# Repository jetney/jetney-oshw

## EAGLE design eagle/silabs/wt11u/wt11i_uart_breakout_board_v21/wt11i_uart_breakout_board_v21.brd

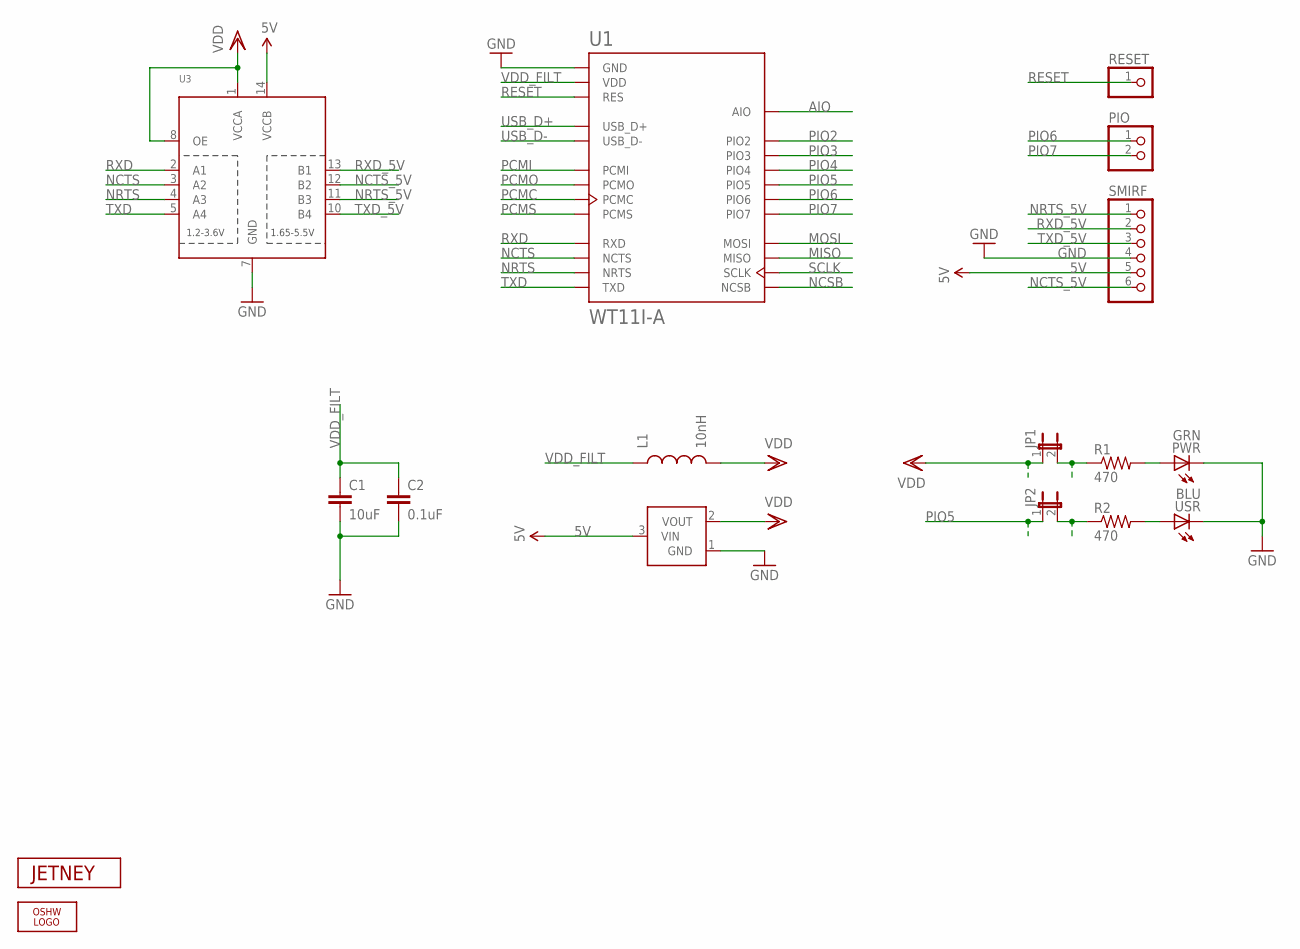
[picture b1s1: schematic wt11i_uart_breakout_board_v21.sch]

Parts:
C1: 10uF; 0603-CAP
C2: 0.1uF; 0603-CAP
JP1, JP2: JUMPER-2SMD-NC; SJ_2S
L1: 10nH; 0603
LOGO1: OSHW_LOGO_FILLX0070-NT; OSHW_FILLX70_NOTEXT
PIO: PINHD-1X2; 1X02
PWR: GRN; CHIPLED_0805
R1, R2: 470; 0603-RES
RESET: PINHD-1X1; 1X01
SMIRF: PINHD-1X6; 1X06
U1: WT11I-A
U2: MCP1700; SOT23-3
U3: TXB0104PWR; TSSOP14
U$4: JETNEY-LOGO-12
USR: BLU; CHIPLED_0805

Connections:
5V: SMIRF.5, U2.3 (VIN), U3.14 (VCCB)
AIO: U1.AIO
GND: C1.2, C2.2, PWR.C, SMIRF.4, U1.GND, U1.GND@2 (GND), U1.GND@3 (GND), U1.GND@4 (GND), U2.1 (GND), U3.7 (GND), USR.C
MISO: U1.MISO
MOSI: U1.MOSI
unnamed: PWR.A, R1.2
unnamed: R2.2, USR.A
unnamed: JP2.2, R2.1
NCSB: U1.NCSB
NCTS: U1.NCTS, U3.3 (A2)
NCTS_5V: SMIRF.6, U3.12 (B2)
NRTS: U1.NRTS, U3.4 (A3)
NRTS_5V: SMIRF.1, U3.11 (B3)
PCMC: U1.PCMC
PCMI: U1.PCMI
PCMO: U1.PCMO
PCMS: U1.PCMS
PIO2: U1.PIO2
PIO3: U1.PIO3
PIO4: U1.PIO4
PIO5: JP2.1, U1.PIO5
PIO6: PIO.1, U1.PIO6
PIO7: PIO.2, U1.PIO7
RESET: RESET.1, U1.RES
RXD: U1.RXD, U3.2 (A1)
RXD_5V: SMIRF.2, U3.13 (B1)
SCLK: U1.SCLK
TXD: U1.TXD, U3.5 (A4)
TXD_5V: SMIRF.3, U3.10 (B4)
USB_D+: U1.USB_D+
USB_D-: U1.USB_D-
VDD: JP1.1, L1.2, U2.2 (VOUT), U3.1 (VCCA), U3.8 (OE)
VDDJP1: JP1.2, R1.1
VDD_FILT: C1.1, C2.1, L1.1, U1.VDD, U1.VDD@2 (VDD)

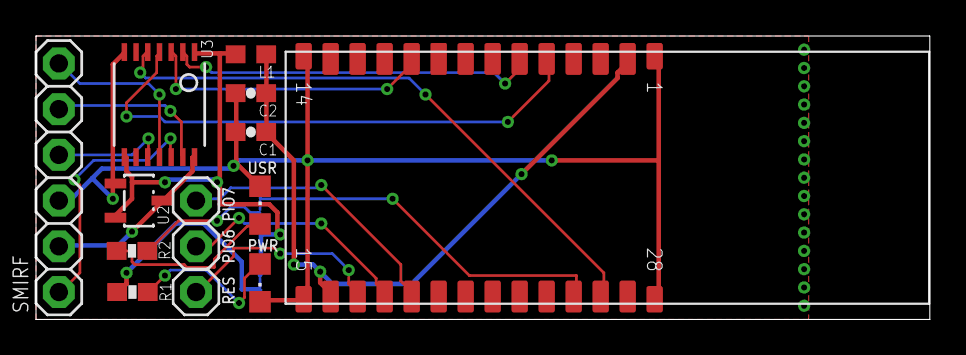
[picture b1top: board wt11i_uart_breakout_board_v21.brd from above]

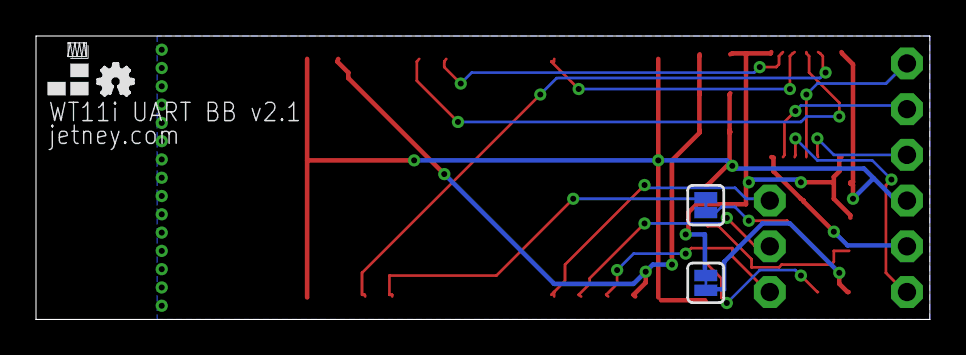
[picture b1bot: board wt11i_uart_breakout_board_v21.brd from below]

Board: 2 copper layers, 49.7 x 15.7 mm, 17 parts (4 on the bottom side), 20 nets.

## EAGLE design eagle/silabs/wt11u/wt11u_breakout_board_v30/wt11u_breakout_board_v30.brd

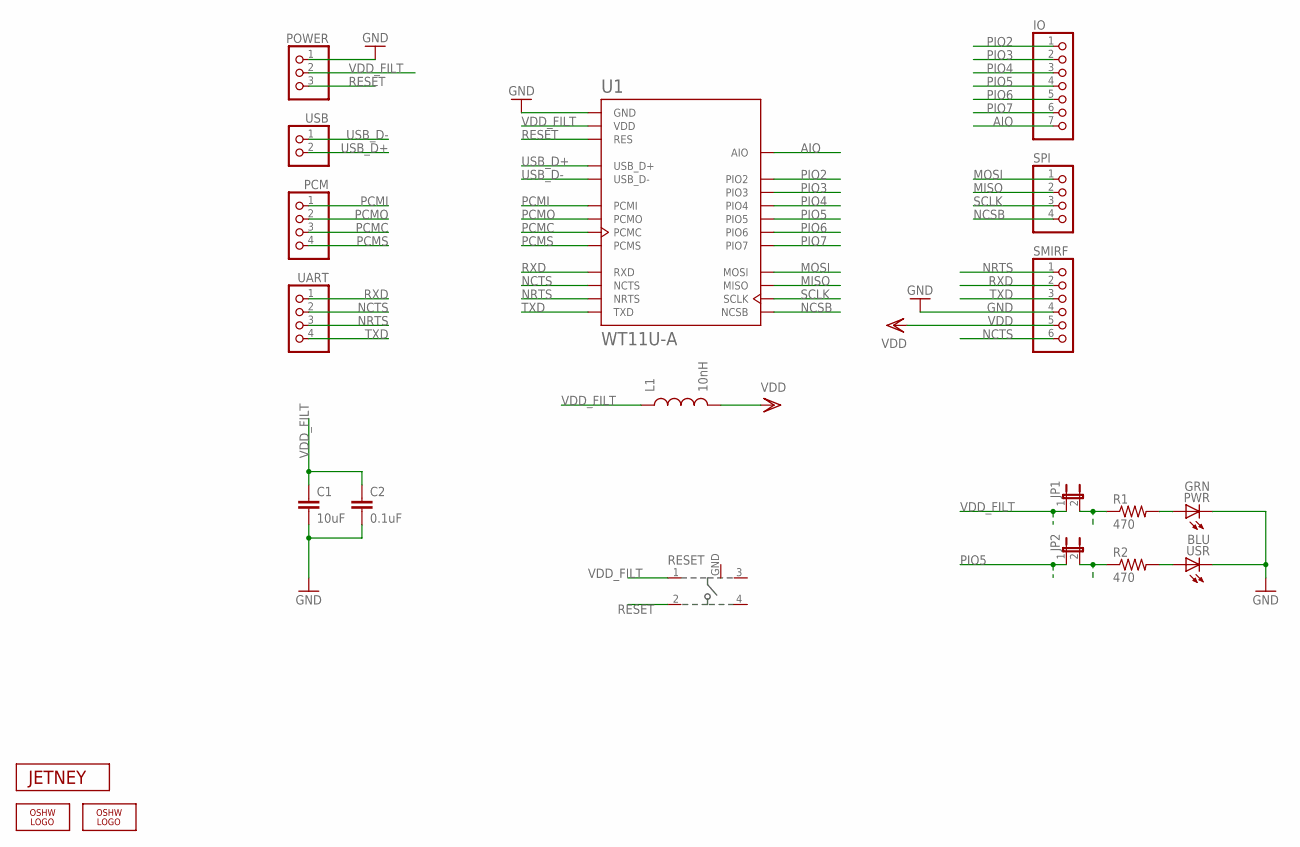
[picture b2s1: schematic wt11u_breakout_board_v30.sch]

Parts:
C1: 10uF; 0603-CAP
C2: 0.1uF; 0603-CAP
IO: PINHD-1X7; 1X07
JP1, JP2: JUMPER-2SMD-NC; SJ_2S
L1: 10nH; 0603
LOGO1, LOGO3: OSHW_LOGO_FILLX0070-NT; OSHW_FILLX70_NOTEXT
PCM: PINHD-1X4; 1X04
POWER: PINHD-1X3; 1X03
PWR: GRN; CHIPLED_0805
R1, R2: 470; 0603-RES
RESET: 101-IG
SMIRF: PINHD-1X6; 1X06
SPI: PINHD-1X4; 1X04
U1: WT11U-A
U$2: JETNEY-LOGO-12
UART: PINHD-1X4; 1X04
USB: PINHD-1X2; 1X02
USR: BLU; CHIPLED_0805

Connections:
AIO: IO.7, U1.AIO
GND: C1.2, C2.2, POWER.1, PWR.C, RESET.GND, SMIRF.4, U1.GND, U1.GND@2 (GND), U1.GND@3 (GND), U1.GND@4 (GND), USR.C
MISO: SPI.2, U1.MISO
MOSI: SPI.1, U1.MOSI
unnamed: PWR.A, R1.2
unnamed: R2.2, USR.A
unnamed: JP2.2, R2.1
NCSB: SPI.4, U1.NCSB
NCTS: SMIRF.6, U1.NCTS, UART.2
NRTS: SMIRF.1, U1.NRTS, UART.3
PCMC: PCM.3, U1.PCMC
PCMI: PCM.1, U1.PCMI
PCMO: PCM.2, U1.PCMO
PCMS: PCM.4, U1.PCMS
PIO2: IO.1, U1.PIO2
PIO3: IO.2, U1.PIO3
PIO4: IO.3, U1.PIO4
PIO5: IO.4, JP2.1, U1.PIO5
PIO6: IO.5, U1.PIO6
PIO7: IO.6, U1.PIO7
RESET: POWER.3, RESET.2, U1.RES
RXD: SMIRF.2, U1.RXD, UART.1
SCLK: SPI.3, U1.SCLK
TXD: SMIRF.3, U1.TXD, UART.4
USB_D+: U1.USB_D+, USB.2
USB_D-: U1.USB_D-, USB.1
VDD: L1.2, SMIRF.5
VDDJP1: JP1.2, R1.1
VDD_FILT: C1.1, C2.1, JP1.1, L1.1, POWER.2, RESET.1, U1.VDD, U1.VDD@2 (VDD)

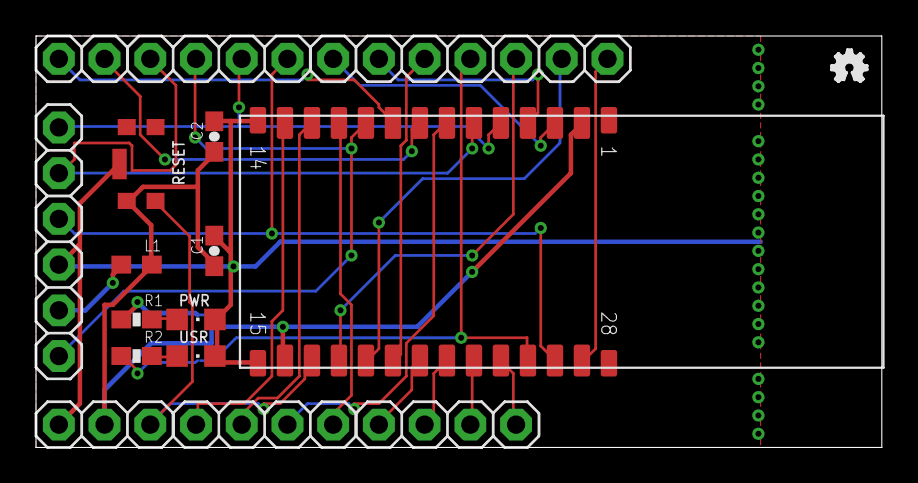
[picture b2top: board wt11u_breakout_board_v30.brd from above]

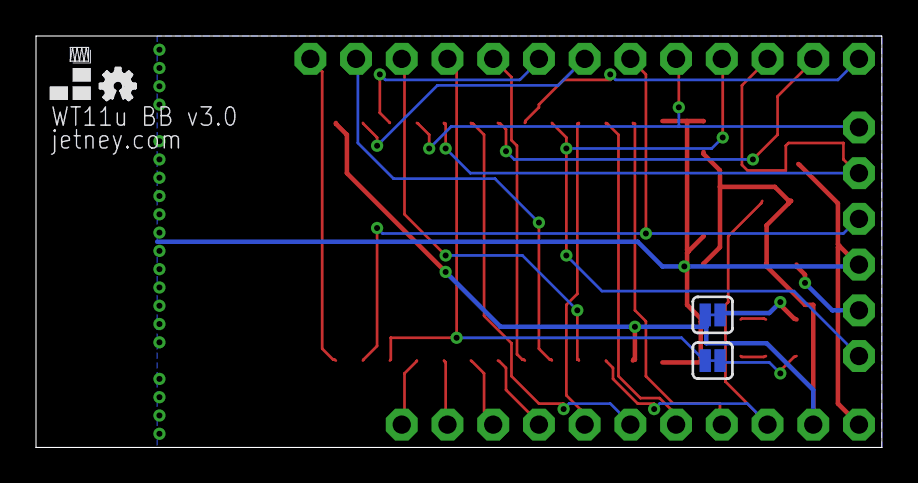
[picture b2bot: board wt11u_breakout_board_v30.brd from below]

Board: 2 copper layers, 47.0 x 22.9 mm, 21 parts (4 on the bottom side), 29 nets.

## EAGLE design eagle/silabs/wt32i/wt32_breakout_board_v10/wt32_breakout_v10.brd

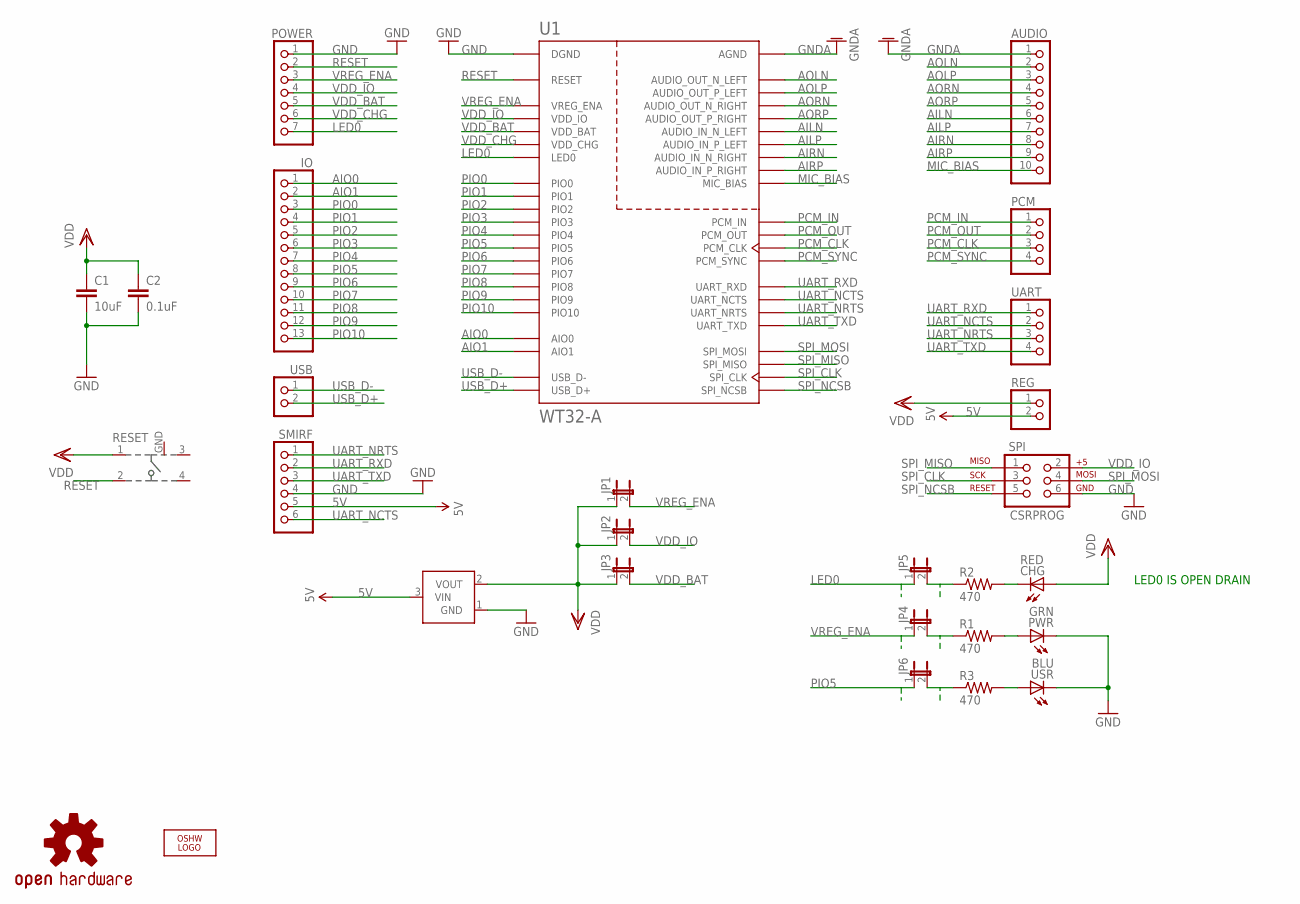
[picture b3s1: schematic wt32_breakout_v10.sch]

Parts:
AUDIO: PINHD-1X10; 1X10
C1: 10uF; 0603-CAP
C2: 0.1uF; 0603-CAP
CHG: RED; CHIPLED_0805
IO: PINHD-1X13; 1X13
JP1, JP2, JP3: JUMPER-2PTH; 1X02
JP4, JP5, JP6: JUMPER-2SMD-NC; SJ_2S
LOGO1: OSHW_LOGO_FILLX0070-NT; OSHW_FILLX70_NOTEXT
PCM: PINHD-1X4; 1X04
POWER: PINHD-1X7; 1X07
PWR: GRN; CHIPLED_0805
R1, R2, R3: 470; 0603-RES
REG: PINHD-1X2; 1X02
RESET: 101-IG
SMIRF: PINHD-1X6; 1X06
SPI: CSRPROG; 2X3
U1: WT32-A
U2: MCP1700; SOT23-3
U$5: OSHW-LOGOM; OSHW-LOGO-M
UART: PINHD-1X4; 1X04
USB: PINHD-1X2; 1X02
USR: BLU; CHIPLED_0805

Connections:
5V: REG.2, SMIRF.5, U2.3 (VIN)
AILN: AUDIO.6, U1.AUDIO_IN_N_LEFT
AILP: AUDIO.7, U1.AUDIO_IN_P_LEFT
AIO0: IO.1, U1.AIO0
AIO1: IO.2, U1.AIO1
AIRN: AUDIO.8, U1.AUDIO_IN_N_RIGHT
AIRP: AUDIO.9, U1.AUDIO_IN_P_RIGHT
AOLN: AUDIO.2, U1.AUDIO_OUT_N_LEFT
AOLP: AUDIO.3, U1.AUDIO_OUT_P_LEFT
AORN: AUDIO.4, U1.AUDIO_OUT_N_RIGHT
AORP: AUDIO.5, U1.AUDIO_OUT_P_RIGHT
GND: C1.2, C2.2, POWER.1, PWR.C, RESET.GND, SMIRF.4, SPI.6, U1.DGND, U1.DGND@2 (DGND), U1.DGND@3 (DGND), U1.DGND@4 (DGND), U1.DGND@5 (DGND), U2.1 (GND), USR.C
GNDA: AUDIO.1, U1.AGND, U1.AGND@2 (AGND), U1.AGND@3 (AGND)
LED0: JP5.1, POWER.7, U1.LED0
MIC_BIAS: AUDIO.10, U1.MIC_BIAS
unnamed: PWR.A, R1.2
unnamed: CHG.C, R2.2
unnamed: R3.2, USR.A
unnamed: JP6.2, R3.1
unnamed: JP4.2, R1.1
unnamed: JP5.2, R2.1
PCM_CLK: PCM.3, U1.PCM_CLK
PCM_IN: PCM.1, U1.PCM_IN
PCM_OUT: PCM.2, U1.PCM_OUT
PCM_SYNC: PCM.4, U1.PCM_SYNC
PIO0: IO.3, U1.PIO0
PIO1: IO.4, U1.PIO1
PIO2: IO.5, U1.PIO2
PIO3: IO.6, U1.PIO3
PIO4: IO.7, U1.PIO4
PIO5: IO.8, JP6.1, U1.PIO5
PIO6: IO.9, U1.PIO6
PIO7: IO.10, U1.PIO7
PIO8: IO.11, U1.PIO8
PIO9: IO.12, U1.PIO9
PIO10: IO.13, U1.PIO10
RESET: POWER.2, RESET.2, U1.RESET
SPI_CLK: SPI.3, U1.SPI_CLK
SPI_MISO: SPI.1, U1.SPI_MISO
SPI_MOSI: SPI.4, U1.SPI_MOSI
SPI_NCSB: SPI.5, U1.SPI_NCSB
UART_NCTS: SMIRF.6, U1.UART_NCTS, UART.2
UART_NRTS: SMIRF.1, U1.UART_NRTS, UART.3
UART_RXD: SMIRF.2, U1.UART_RXD, UART.1
UART_TXD: SMIRF.3, U1.UART_TXD, UART.4
USB_D+: U1.USB_D+, USB.2
USB_D-: U1.USB_D-, USB.1
VDD: C1.1, C2.1, CHG.A, JP1.1, JP2.1, JP3.1, REG.1, RESET.1, U2.2 (VOUT)
VDD_BAT: JP3.2, POWER.5, U1.VDD_BAT
VDD_CHG: POWER.6, U1.VDD_CHG
VDD_IO: JP2.2, POWER.4, SPI.2, U1.VDD_IO
VREG_ENA: JP1.2, JP4.1, POWER.3, U1.VREG_ENA

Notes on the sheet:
LED0 IS OPEN DRAIN

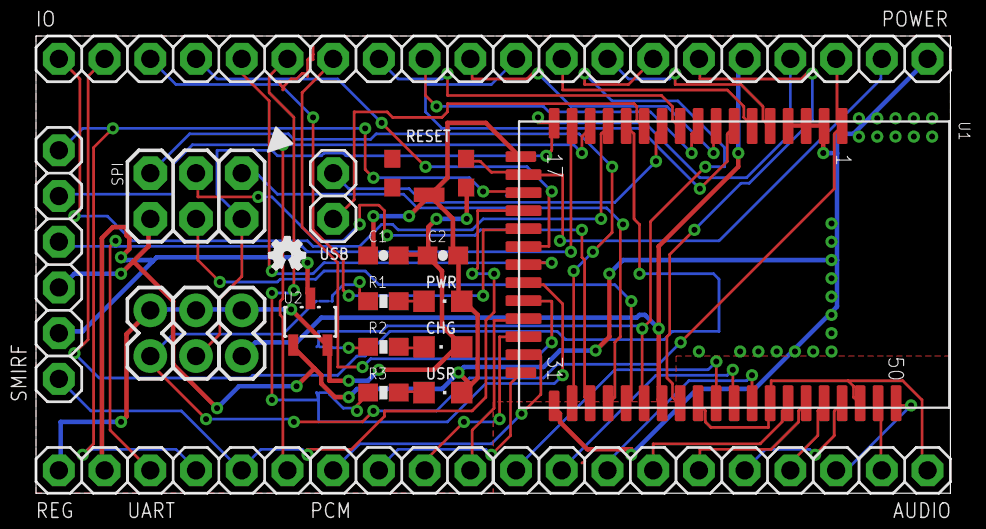
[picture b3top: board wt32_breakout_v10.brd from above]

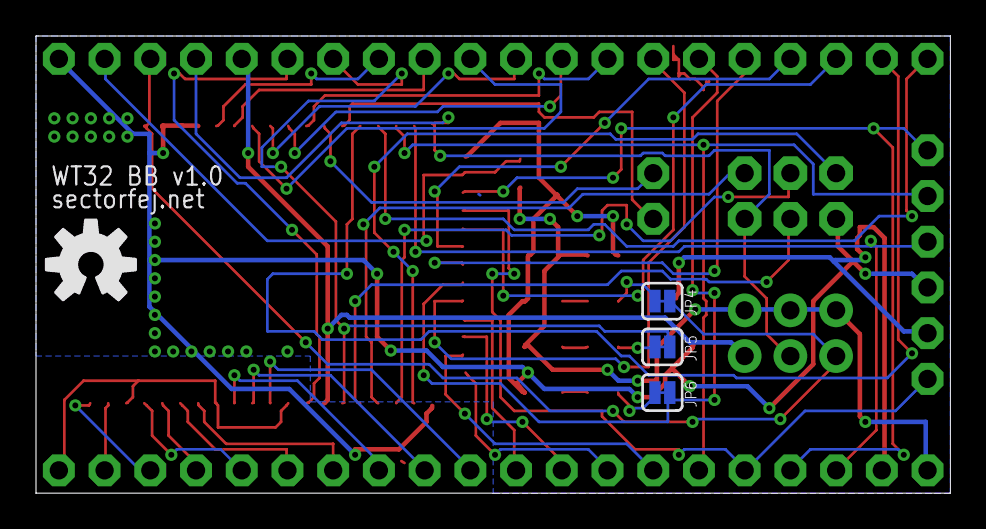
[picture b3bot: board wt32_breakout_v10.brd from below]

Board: 2 copper layers, 50.8 x 25.4 mm, 28 parts (4 on the bottom side), 52 nets.

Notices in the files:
parts and their libraries:
SparkFun: Licensing: CC v3.0 Share-Alike You are welcome to use this library for commercial purposes.
